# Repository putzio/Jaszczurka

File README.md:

# Jaszczurka

This is a project of a lizard robot, which uses 3 servomotors to move

### Program

The microcontroller we have used is AtMega 328p (the same is used in Arduino UNO).
You can find the code in "Jaszczurka" directory

### PCB
The PCB was created in Eagle and you can find it in the "Traszka" directory

### Mechanical construction
The robot was modeled in Fusion 360 and 3D printed:
https://a360.co/3q6MQ5f

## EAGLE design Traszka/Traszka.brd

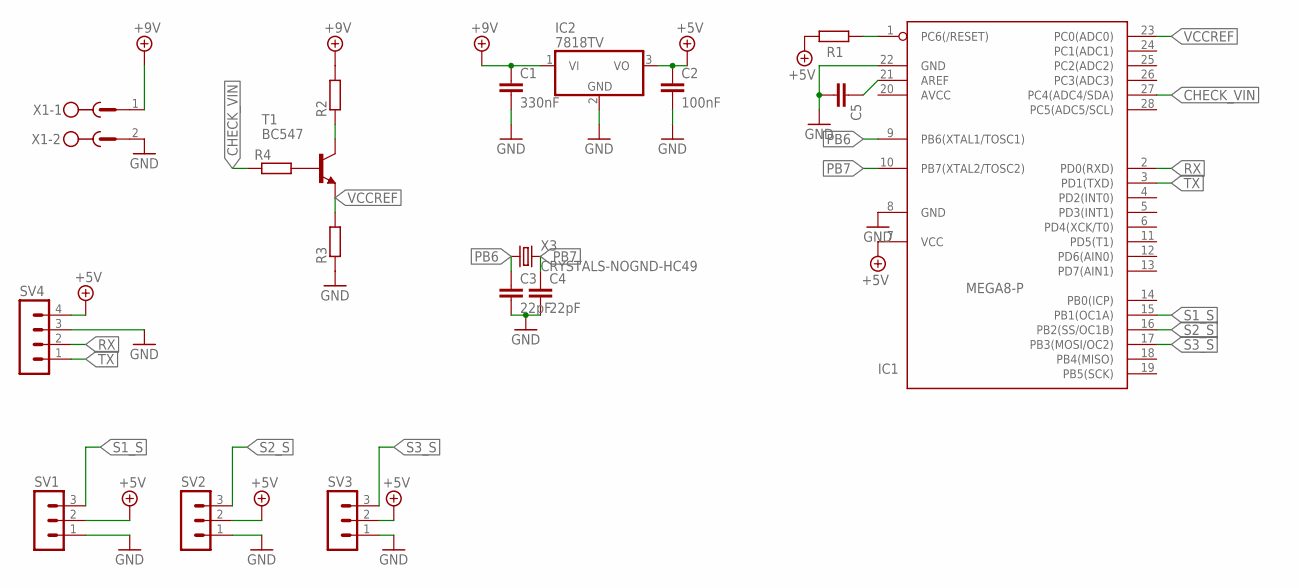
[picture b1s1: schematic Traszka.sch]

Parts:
C1: 330nF; C050-024X044
C2: 100nF; C050-024X044
C3, C4: 22pF; C050-024X044
C5: C-EU050-024X044; C050-024X044
IC1: MEGA8-P; DIL28-3
IC2: 7818TV; TO220V
R1, R2, R4: R-EU_0204/7; 0204/7
R3: R-EU_0204/5; 0204/5
SV1, SV2, SV3: MA03-1
SV4: MA04-1
T1: BC547; TO92
X1: MSTBV2
X3: CRYSTALS-NOGND-HC49; HC49

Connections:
+5V: C2.1, IC1.7 (VCC), IC2.3 (VO), R1.1, SV1.2, SV2.2, SV3.2, SV4.4
+9V: C1.1, IC2.1 (VI), R2.2, X1.1
AVCC: IC1.20 (AVCC)
CHECK_VIN: IC1.27 (PC4(ADC4/SDA)), R4.1
GND: C1.2, C2.2, C3.2, C4.2, C5.2, IC1.8 (GND), IC1.22 (GND), IC2.2 (GND), R3.1, SV1.1, SV2.1, SV3.1, SV4.3, X1.2
unnamed: IC1.1 (PC6(/RESET)), R1.2
unnamed: C5.1, IC1.21 (AREF)
unnamed: R2.1, T1.3 (C)
unnamed: R4.2, T1.2 (B)
PB6: C3.1, IC1.9 (PB6(XTAL1/TOSC1)), X3.1
PB7: C4.1, IC1.10 (PB7(XTAL2/TOSC2)), X3.2
RX: IC1.2 (PD0(RXD)), SV4.2
S1_S: IC1.15 (PB1(OC1A)), SV1.3
S2_S: IC1.16 (PB2(SS/OC1B)), SV2.3
S3_S: IC1.17 (PB3(MOSI/OC2)), SV3.3
TX: IC1.3 (PD1(TXD)), SV4.1
VCCREF: IC1.23 (PC0(ADC0)), R3.2, T1.1 (E)

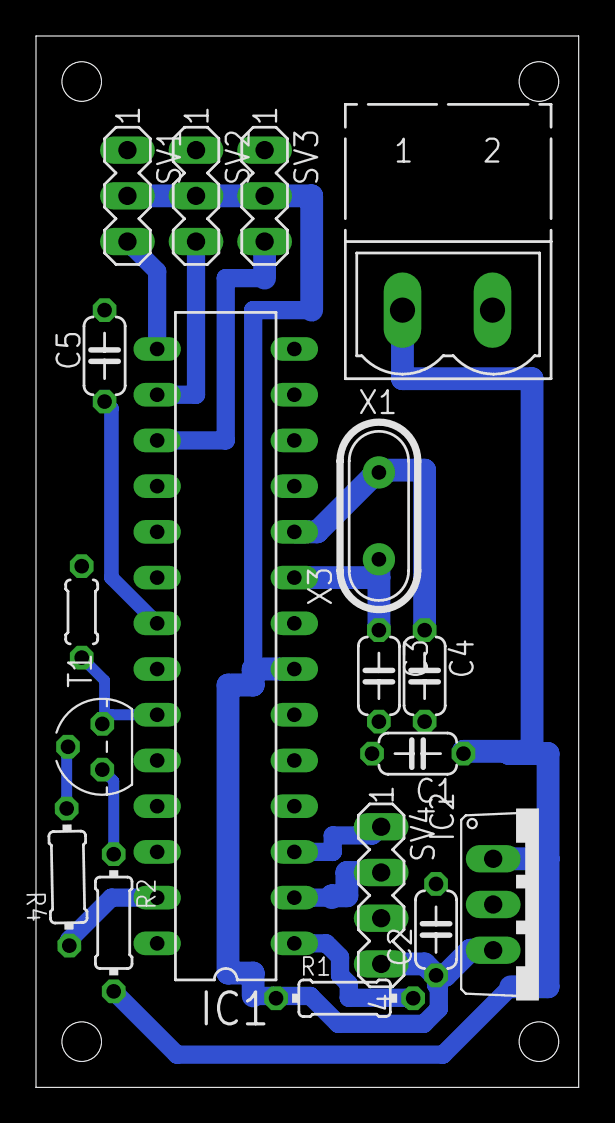
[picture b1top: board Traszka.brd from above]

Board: 2 copper layers, 30.1 x 58.4 mm, 18 parts (0 on the bottom side), 16 nets.

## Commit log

2021-02-23 Elektronika v1
2021-02-23 nowy dokument
2021-03-09 brd and UART Test
2021-03-09 wrong files are deleted
2021-03-10 test
2021-03-13 UART is working, F Changed from 12Mhz to 16MHz
2021-03-14 UART receve interrupt
2021-03-15 Code improvement
2021-03-15 I guess it's the final version
2021-03-15 C'mon, I know why we use 16MHz oscillator
2021-03-20 the move function is using timer instead of delay
2021-04-13 Final version
2021-05-11 Excel file to choose the right resistors
2022-03-02 Remove unnecessary components
2022-03-02 .gitignore update
2022-03-02 fixing .sch and .brd checking battery
2022-03-02 Stop mode
